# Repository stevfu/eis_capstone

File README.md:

# eis_capstone
Utilization of Electrochemical Impedance Spectroscopy for the Detection of Drugs

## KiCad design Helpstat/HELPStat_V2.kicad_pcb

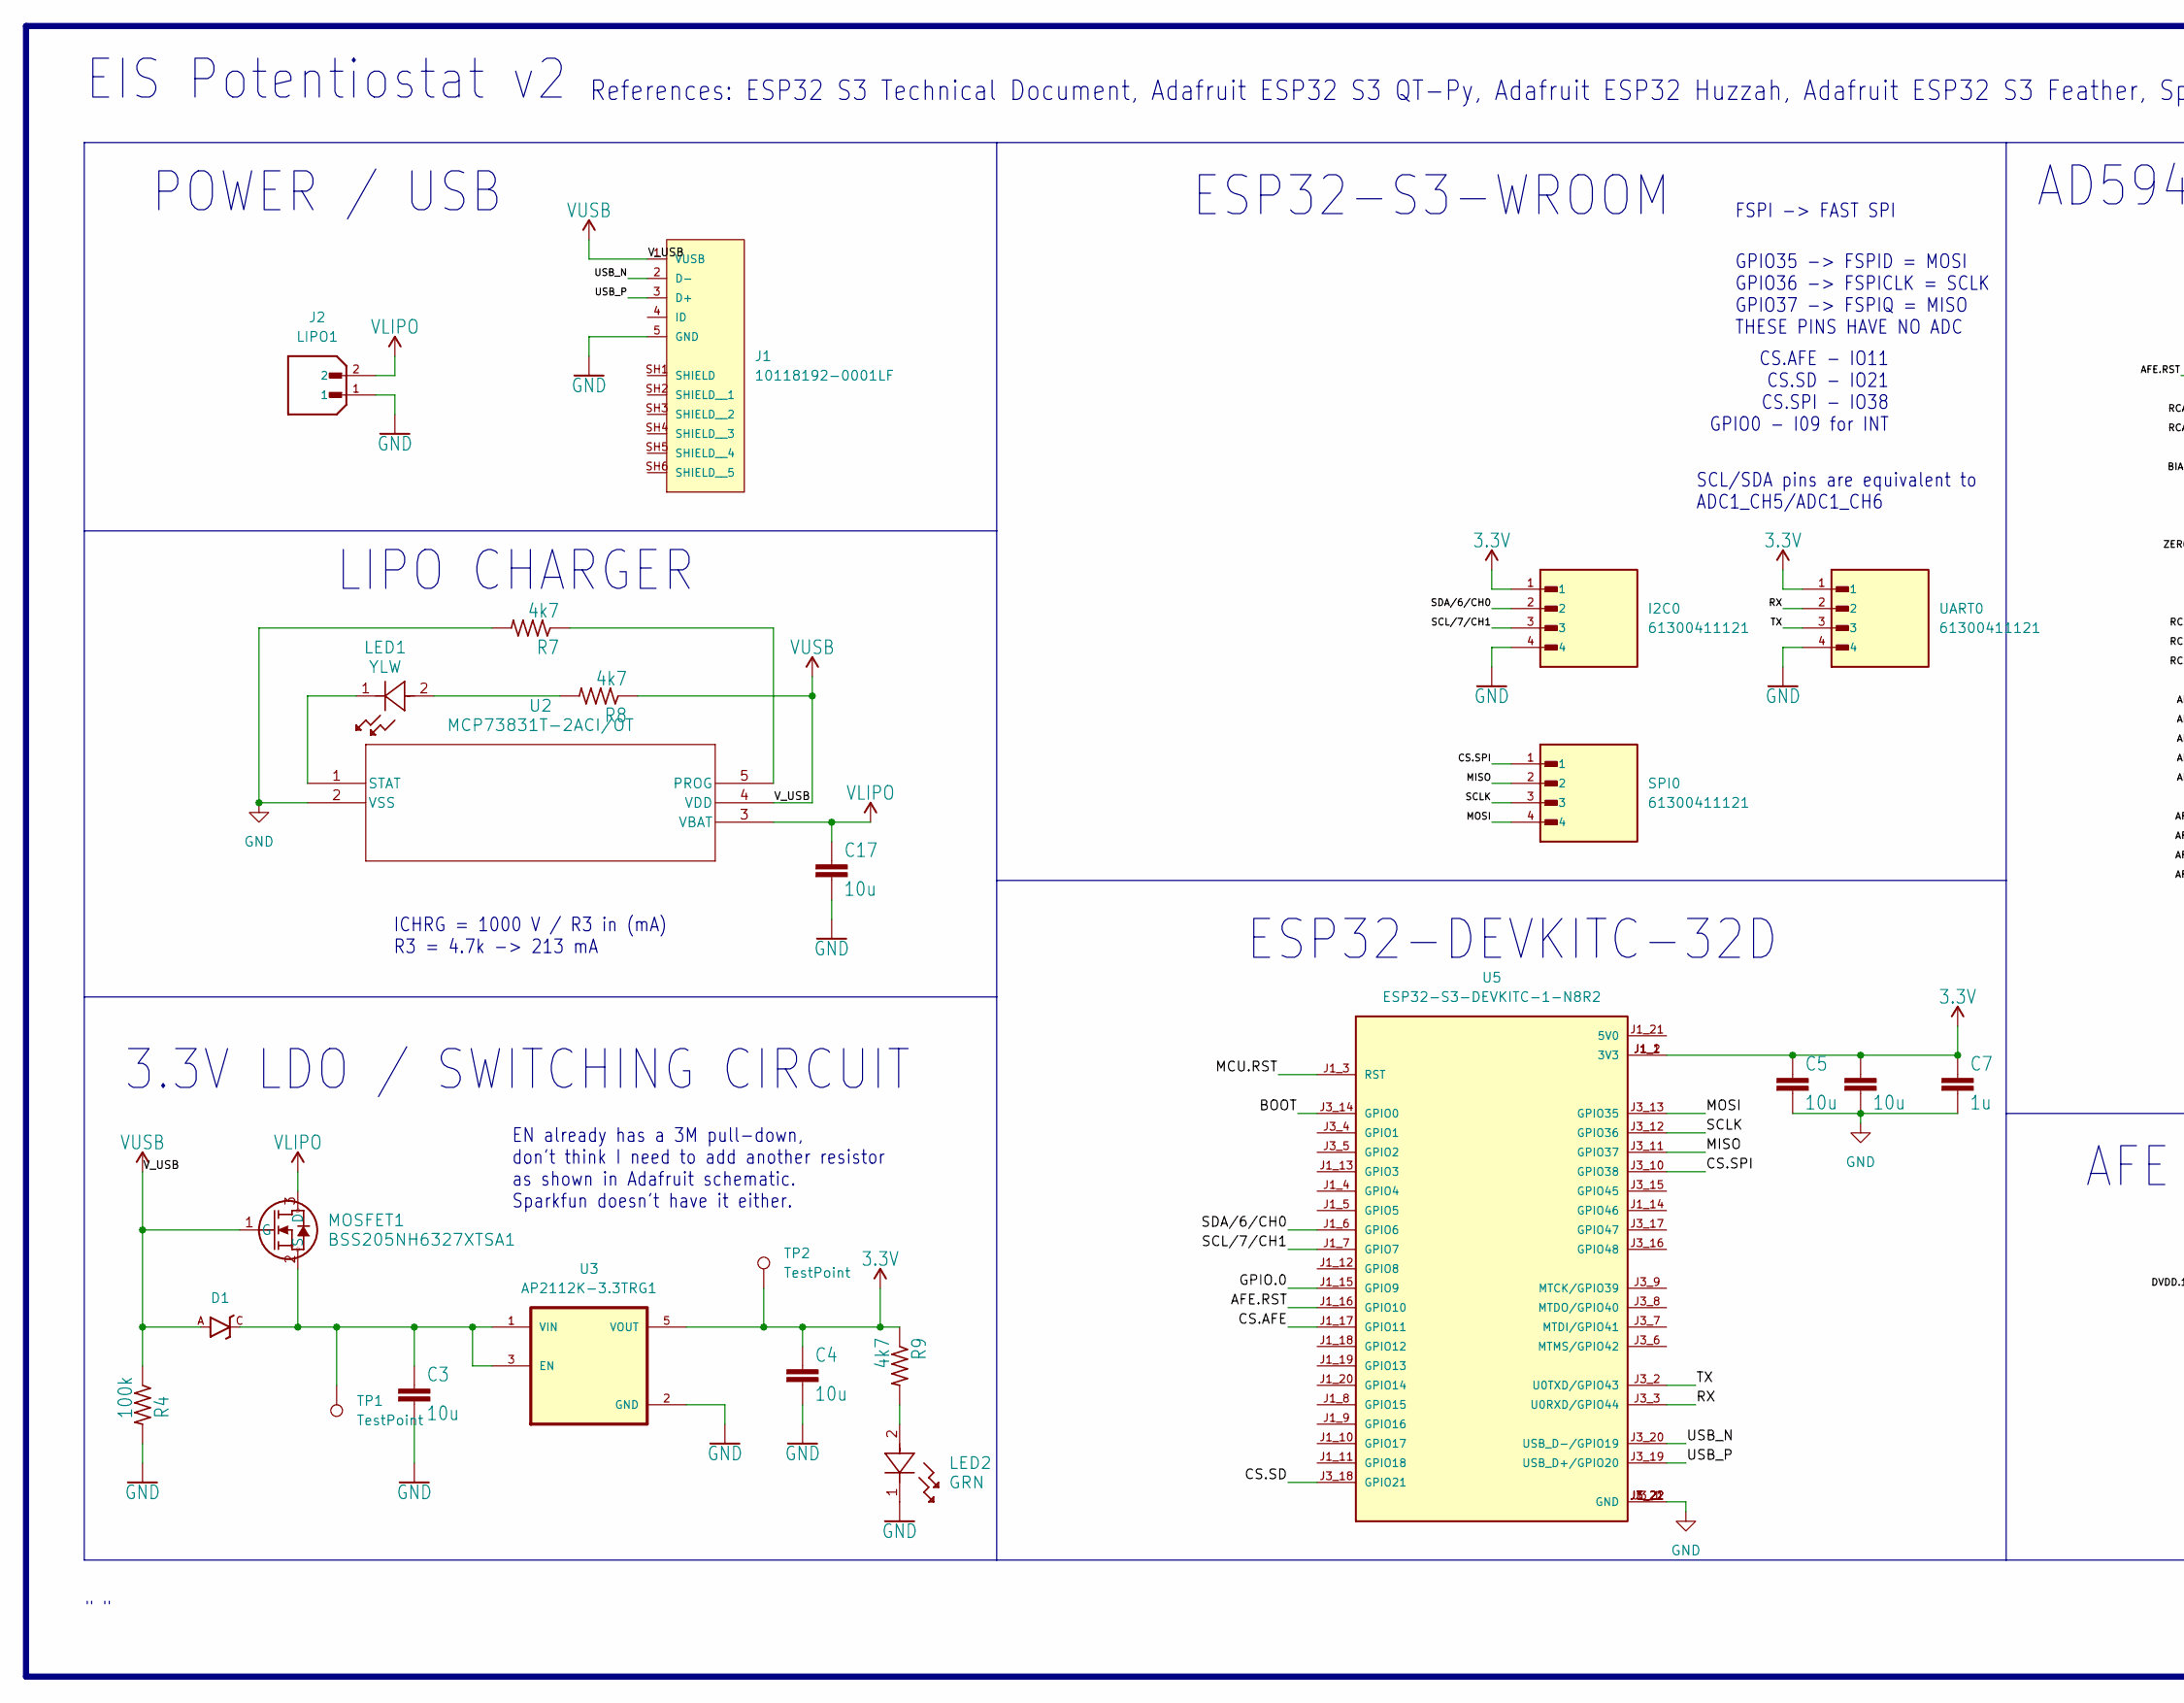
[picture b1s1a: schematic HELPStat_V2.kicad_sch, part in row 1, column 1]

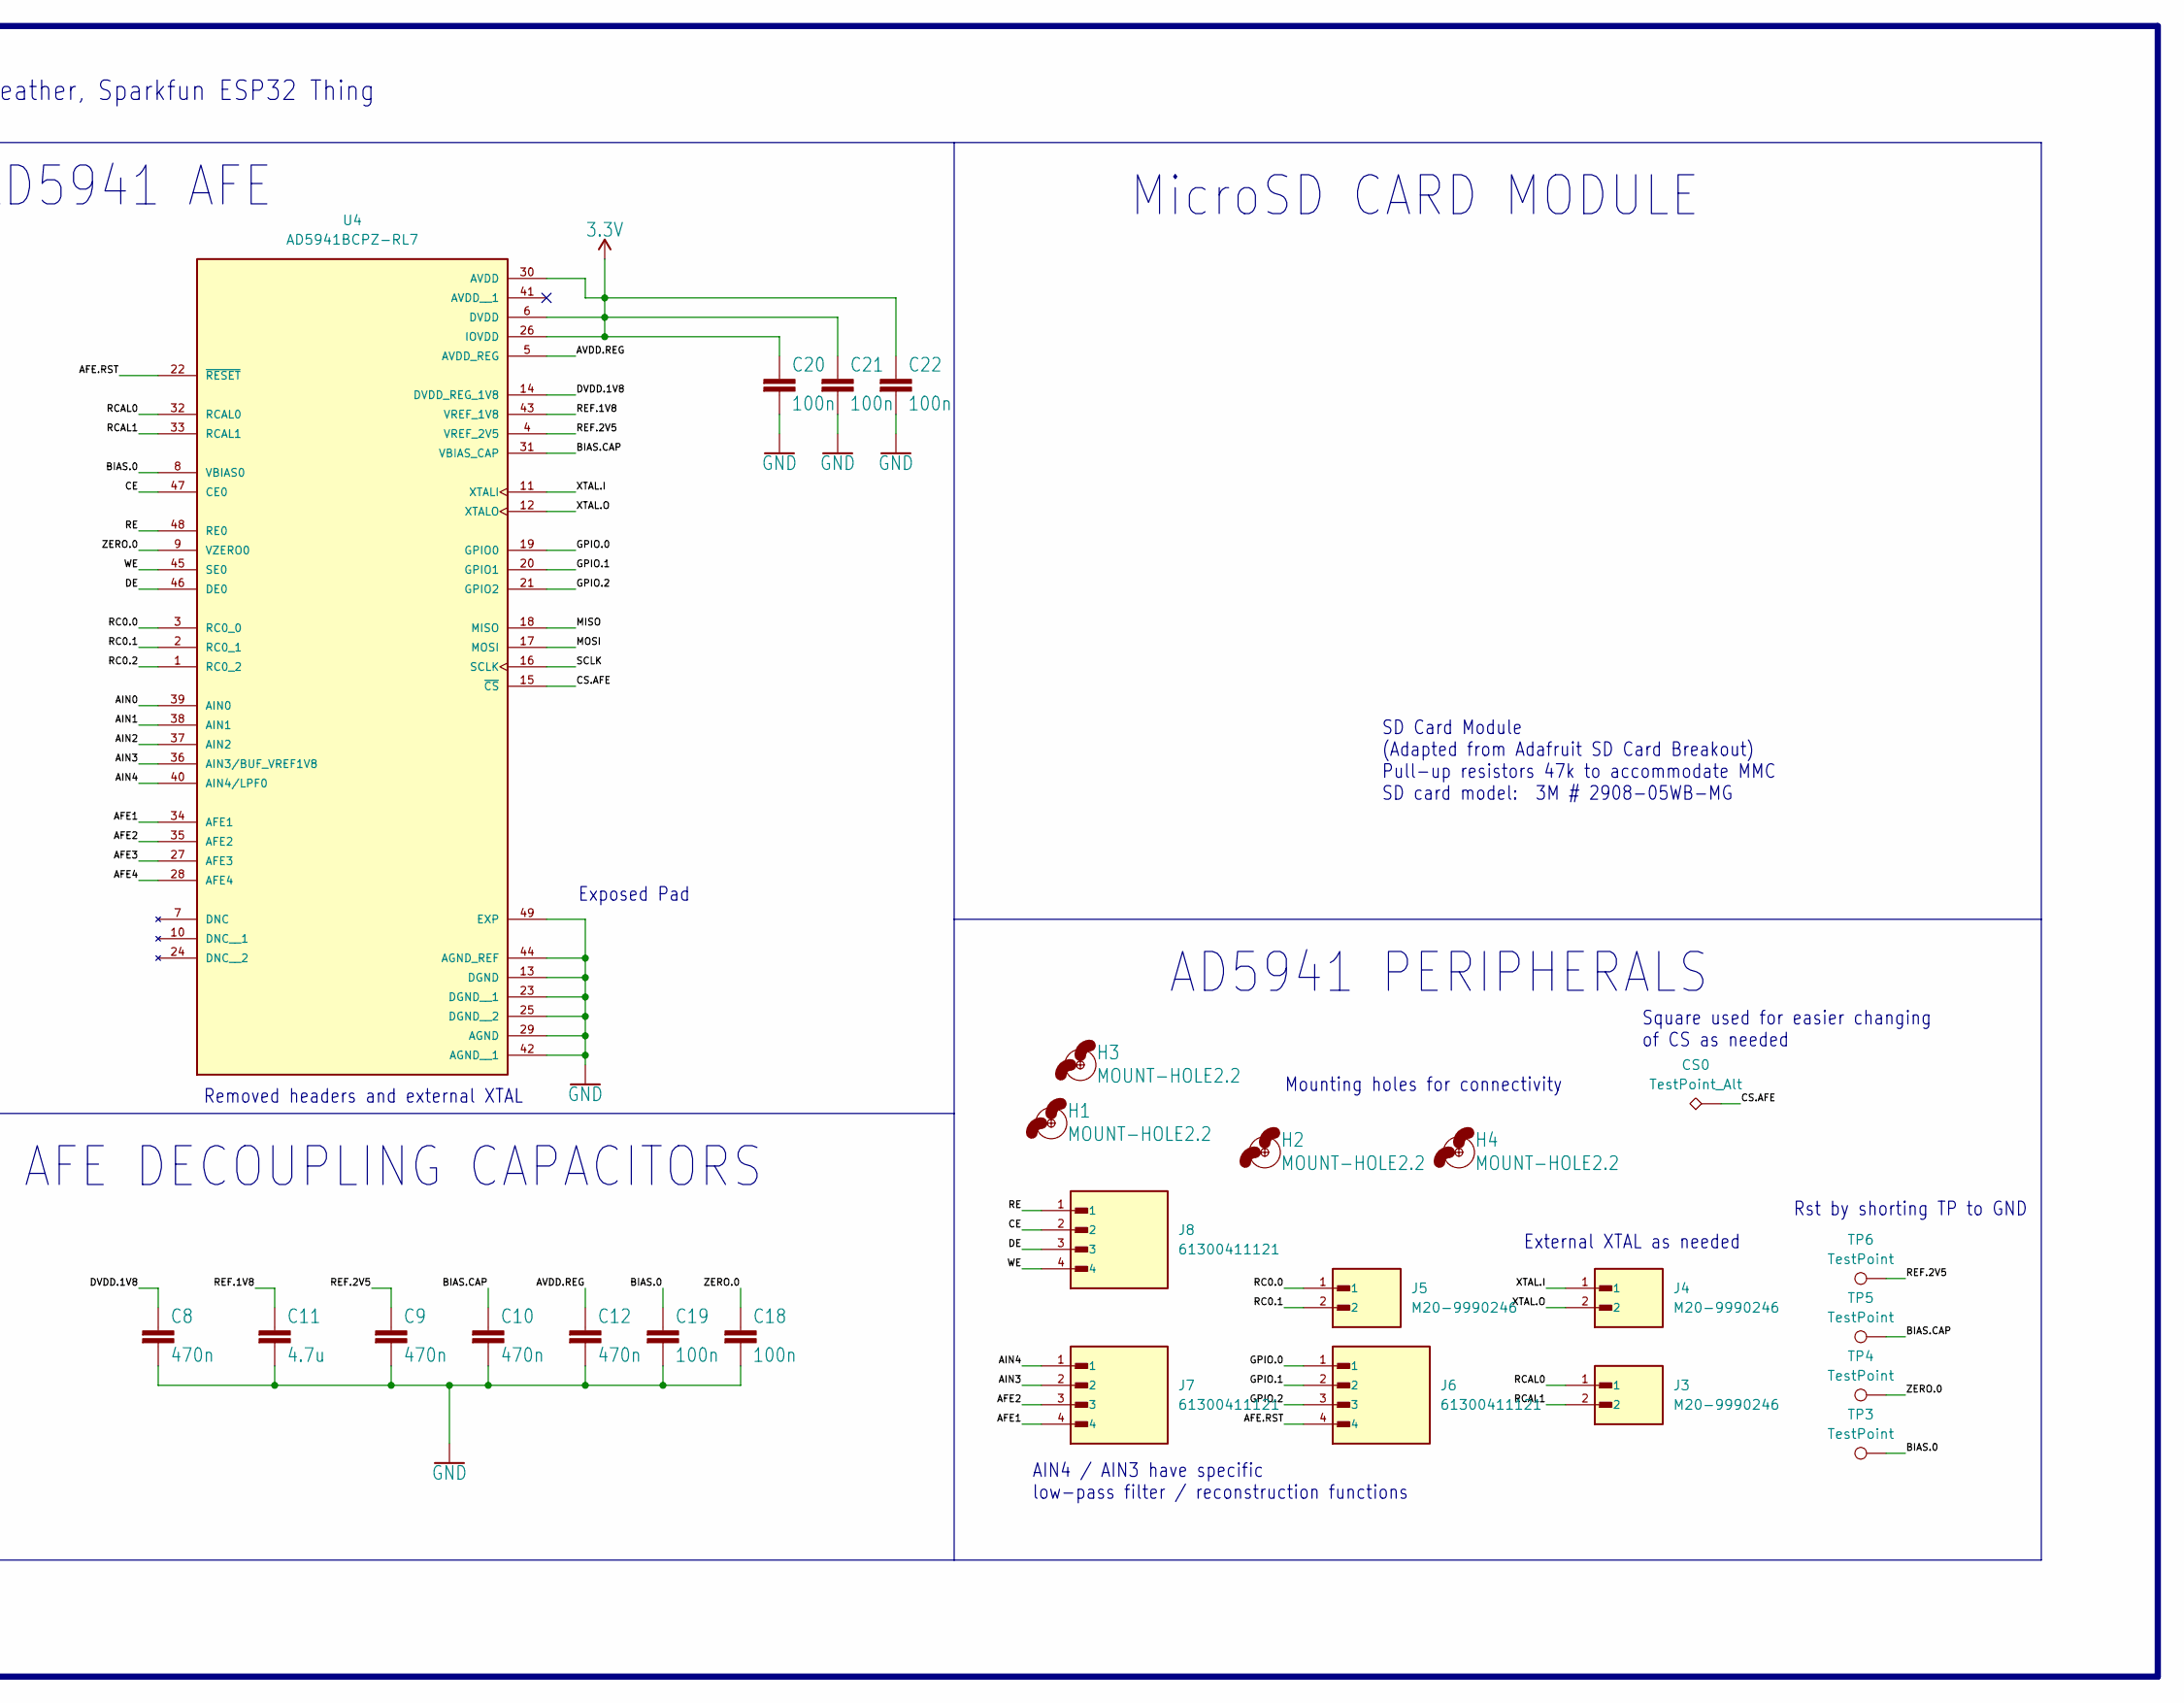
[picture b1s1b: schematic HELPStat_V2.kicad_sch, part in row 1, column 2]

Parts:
C3, C4, C5, C6, C17: 10u; C_0603_1608Metric; Part Number LMK107BBJ106MALT
C7: 1u; C_0603_1608Metric; Part Number CL10B105KP8NNNC
C8, C9, C10, C12: 470n; C_0603_1608Metric; Part Number TMK107B7474KA-TR
C11: 4.7u; C_0603_1608Metric; Part Number LMK107BJ475KA-T
C18, C19, C20, C21, C22: 100n; C_0603_1608Metric; Part Number CC0603KRX7R7BB104
CS0: TestPoint_Alt; TestPoint_Pad_2.0x2.0mm
D1: BAT20JFILM; SOD-323; Part Number BAT20JFILM
H1, H2, H3, H4: MOUNT-HOLE2.2; MountingHole_2.2mm_M2_Pad
I2C0: 61300411121; Part Number 61300411121
J1: 10118192-0001LF; AMPHENOL_10118192-0001LF; Part Number 10118192-0001LF
J2: LIPO1; JST_B2B-XH-A; Part Number B2B-XH-A:JST_B2B-XH-A
J3, J4, J5: M20-9990246; HARWIN_M20-9990246; Part Number M20-9990246
J6, J7, J8: 61300411121; Part Number 61300411121
LED1: YLW; LED_00-R18_OSR; Part Number GY PSLM31.13-HQHS-5F5G-L2M2-100-R18
LED2: GRN; LED_00-R18_OSR; Part Number GT PSLM31.13-HRHT-26-KM-100-R18
MOSFET1: BSS205NH6327XTSA1; PG-SOT23-3-5_INF; Part Number BSS205NH6327XTSA1
R4: 100k; R_0603_1608Metric; Part Number RC0603FR-07100KL
R7, R8, R9: 4k7; R_0603_1608Metric; Part Number RC0603FR-074K7L
SPI0: 61300411121; Part Number 61300411121
TP1, TP2, TP3, TP4, TP5, TP6: TestPoint; TestPoint_Pad_D1.0mm
U2: MCP73831T-2ACI/OT; SOT-23-5_MC_MCH; Part Number MCP73831T-2ACI/OT
U3: AP2112K-3.3TRG1; SOT95P285X140-5N; Part Number AP2112K-3.3TRG1
U4: AD5941BCPZ-RL7; QFN50P700X700X80-49N; Part Number AD5941BCPZ-RL7
U5: ESP32-S3-DEVKITC-1-N8R2; XCVR_ESP32-S3-DEVKITC-1-N8R2; Part Number ESP32-S3-DEVKITC-1-N8R2
UART0: 61300411121; Part Number 61300411121

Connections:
3.3V: C4.1, C5.1, C6.1, C7.1, C20.1, C21.1, C22.1, I2C0.1, R9.1, TP2.1, U3.5 (VOUT), U4.6 (DVDD), U4.26 (IOVDD), U4.30 (AVDD), U5.J1_1 (3V3), U5.J1_2 (3V3), UART0.1
/AFE1: J7.4, U4.34 (AFE1)
/AFE2: J7.3, U4.35 (AFE2)
/AFE3: U4.27 (AFE3)
/AFE4: U4.28 (AFE4)
/AFE.RST: J6.4, U4.22 (~RESET), U5.J1_16 (GPIO10)
/AIN0: U4.39 (AIN0)
/AIN1: U4.38 (AIN1)
/AIN2: U4.37 (AIN2)
/AIN3: J7.2, U4.36 (AIN3/BUF_VREF1V8)
/AIN4: J7.1, U4.40 (AIN4/LPF0)
/AVDD.REG: C12.1, U4.5 (AVDD_REG)
/BIAS.0: C19.1, TP3.1, U4.8 (VBIAS0)
/BIAS.CAP: C10.1, TP5.1, U4.31 (VBIAS_CAP)
/BOOT: U5.J3_14 (GPIO0)
/CE: J8.2, U4.47 (CE0)
/CS.AFE: CS0.1, U4.15 (~CS), U5.J1_17 (GPIO11)
/CS.SD: U5.J3_18 (GPIO21)
/CS.SPI: SPI0.1, U5.J3_10 (GPIO38)
/DE: J8.3, U4.46 (DE0)
/DVDD.1V8: C8.1, U4.14 (DVDD_REG_1V8)
/GPIO.0: J6.1, U4.19 (GPIO0), U5.J1_15 (GPIO9)
/GPIO.1: J6.2, U4.20 (GPIO1)
/GPIO.2: J6.3, U4.21 (GPIO2)
/MCU.RST: U5.J1_3 (RST)
/MISO: SPI0.2, U4.18 (MISO), U5.J3_11 (GPIO37)
/MOSI: SPI0.4, U4.17 (MOSI), U5.J3_13 (GPIO35)
/RC0.0: J5.1, U4.3 (RC0_0)
/RC0.1: J5.2, U4.2 (RC0_1)
/RC0.2: U4.1 (RC0_2)
/RCAL0: J3.1, U4.32 (RCAL0)
/RCAL1: J3.2, U4.33 (RCAL1)
/RE: J8.1, U4.48 (RE0)
/REF.1V8: C11.1, U4.43 (VREF_1V8)
/REF.2V5: C9.1, TP6.1, U4.4 (VREF_2V5)
/RX: U5.J3_3 (U0RXD/GPIO44), UART0.2
/SCLK: SPI0.3, U4.16 (SCLK), U5.J3_12 (GPIO36)
/TX: U5.J3_2 (U0TXD/GPIO43), UART0.3
/USB_N: J1.2 (D-), U5.J3_20 (USB_D-/GPIO19)
/USB_P: J1.3 (D+), U5.J3_19 (USB_D+/GPIO20)
/WE: J8.4, U4.45 (SE0)
/XTAL.I: J4.1, U4.11 (XTALI)
/XTAL.O: J4.2, U4.12 (XTALO)
/ZERO.0: C18.1, TP4.1, U4.9 (VZERO0)
GND: C3.2, C4.2, C5.2, C6.2, C7.2, C8.2, C9.2, C10.2, C11.2, C12.2, C17.2, C18.2, C19.2, C20.2, C21.2, C22.2, I2C0.4, J1.5 (GND), J2.1, LED2.1, R4.2, R7.2, U2.2 (VSS), U3.2 (GND), U4.13 (DGND), U4.23 (DGND__1), U4.25 (DGND__2), U4.29 (AGND), U4.42 (AGND__1), U4.44 (AGND_REF), U4.49 (EXP), U5.J1_22 (GND), U5.J3_1 (GND), U5.J3_21 (GND), U5.J3_22 (GND), UART0.4
unnamed: LED1.2, R8.2
unnamed: LED2.2, R9.2
unnamed: C3.1, D1.C, MOSFET1.2 (S), TP1.1, U3.1 (VIN), U3.3 (EN)
unnamed: R7.1, U2.5 (PROG)
unnamed: LED1.1, U2.1 (STAT)
VLIPO: C17.1, J2.2, MOSFET1.3 (D), U2.3 (VBAT)
VUSB: D1.A, J1.1 (VUSB), MOSFET1.1 (G), R4.1, R8.1, U2.4 (VDD)

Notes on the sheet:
MicroSD CARD MODULE
Rst by shorting TP to GND
ESP32-S3-WROOM
EN already has a 3M pull-down, don't think I need to add another resistor as shown in Adafruit schematic. Sparkfun doesn't have it either.
AD5941 PERIPHERALS
ICHRG = 1000 V / R3 in (mA) R3 = 4.7k -> 213 mA
AIN4 / AIN3 have specific low-pass filter / reconstruction functions
Mounting holes for connectivity
CS.AFE - IO11 CS.SD - IO21 CS.SPI - IO38 GPIO0 - I09 for INT
AFE DECOUPLING CAPACITORS
POWER / USB
LIPO CHARGER
Exposed Pad
SCL/SDA pins are equivalent to ADC1_CH5/ADC1_CH6
AD5941 AFE
" "
Square used for easier changing of CS as needed
3.3V LDO / SWITCHING CIRCUIT
References: ESP32 S3 Technical Document, Adafruit ESP32 S3 QT-Py, Adafruit ESP32 Huzzah, Adafruit ESP32 S3 Feather, Sparkfun ESP32 Thing
External XTAL as needed
EIS Potentiostat v2
ESP32-DEVKITC-32D
SD Card Module (Adapted from Adafruit SD Card Breakout) Pull-up resistors 47k to accommodate MMC SD card model: 3M # 2908-05WB-MG
Removed headers and external XTAL
GPIO35 -> FSPID = MOSI GPIO36 -> FSPICLK = SCLK GPIO37 -> FSPIQ = MISO THESE PINS HAVE NO ADC
FSPI -> FAST SPI

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
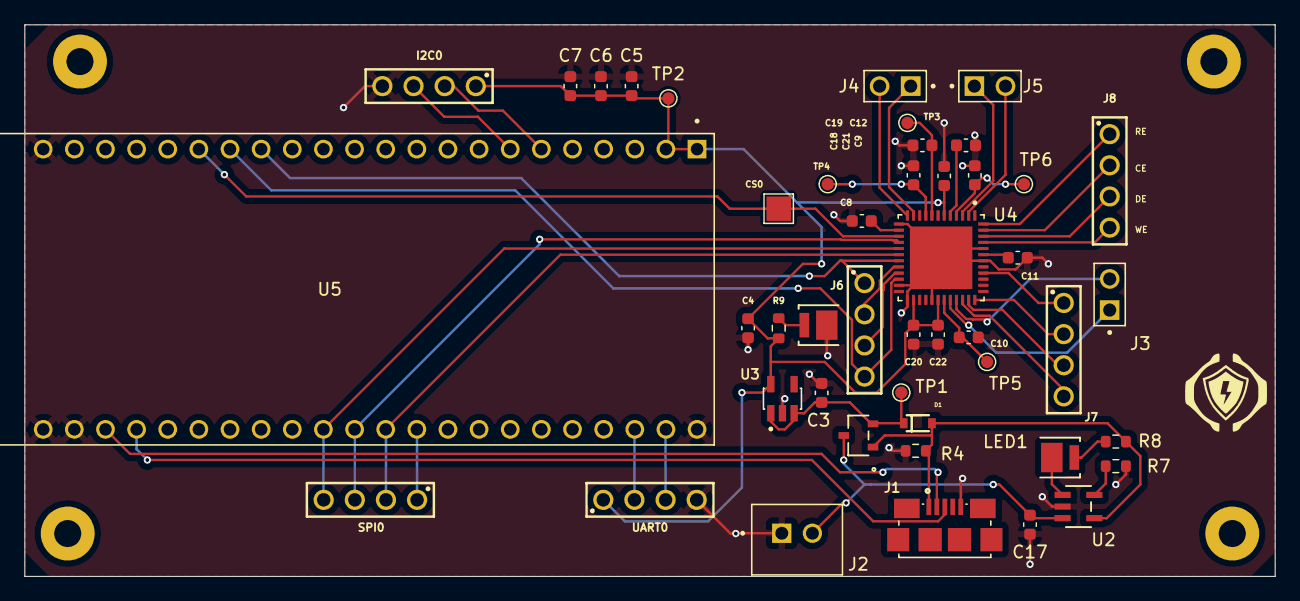
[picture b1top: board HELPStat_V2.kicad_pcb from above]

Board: 2 copper layers, 102.0 x 45.0 mm, 50 parts (0 on the bottom side), 45 nets.

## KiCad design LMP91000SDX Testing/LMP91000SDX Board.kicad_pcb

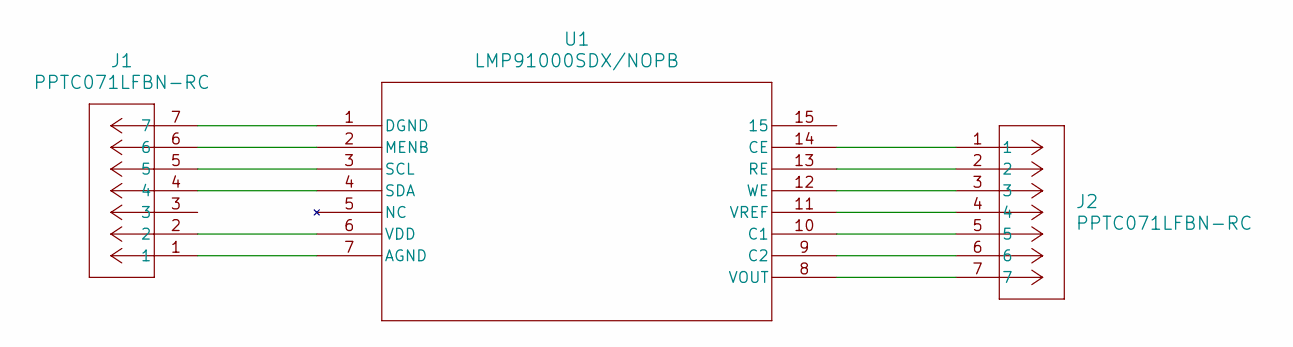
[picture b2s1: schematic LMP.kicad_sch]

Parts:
J1, J2: PPTC071LFBN-RC; CONN_xPxC071LFBN-RC_SUL
U1: LMP91000SDX/NOPB; SDA14B

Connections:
unnamed: J1.1, U1.7 (AGND)
unnamed: J2.5, U1.10 (C1)
unnamed: J2.6, U1.9 (C2)
unnamed: J2.1, U1.14 (CE)
unnamed: J1.7, U1.1 (DGND)
unnamed: J1.6, U1.2 (MENB)
unnamed: J2.2, U1.13 (RE)
unnamed: J1.5, U1.3 (SCL)
unnamed: J1.4, U1.4 (SDA)
unnamed: J1.2, U1.6 (VDD)
unnamed: J2.7, U1.8 (VOUT)
unnamed: J2.4, U1.11 (VREF)
unnamed: J2.3, U1.12 (WE)

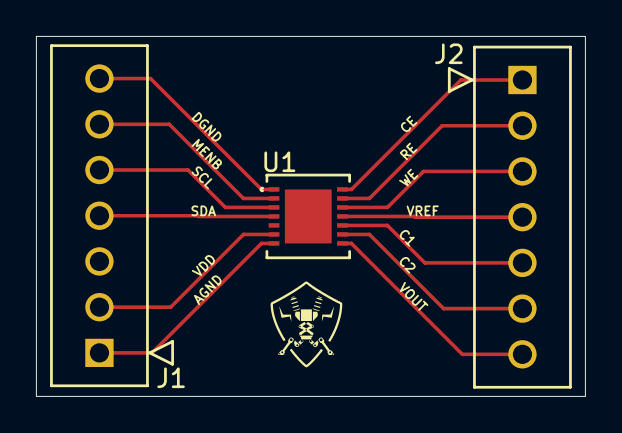
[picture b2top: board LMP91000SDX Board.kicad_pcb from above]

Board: 2 copper layers, 30.5 x 20.0 mm, 3 parts (0 on the bottom side), 13 nets.

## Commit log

2025-03-07 intial commit
2025-03-18 LMP91000SDX Testing
2025-03-19 Testing Board Completed
2025-03-24 Schematic Edits
2025-03-25 Added LMP USP-UART
2025-03-25 LMP USB Update
2025-03-25 deleted laptop duplicates
2025-04-24 Andrew Edits
2025-04-24 Sch Draft Completed
2025-04-25 added firmware template and pcb
2025-04-26 more pcb changes
2025-04-26 BOM CSV added
2025-04-26 CSV and SCH edits
2025-04-28 PCB Touches
2025-04-29 PCB Editted Routes
2025-04-30 Gibby Bub
2025-05-09 pcb v2
2025-05-10 Sch and PCB cleanup/fixes
2025-05-21 extra PCB changes
2025-05-27 working pcb code
2025-06-04 new software
2025-06-11 revisions i think
2025-06-11 hmhmhmhhm
2025-06-26 kk
    kk transform
2025-06-26 ECM calculations
    ECM
2025-06-27 ecm stuffs
2025-06-27 organization, new firmware scripts
2025-06-29 ecm fitting function
    trials
2025-06-30 test cases
2025-07-01 new filter
2025-07-04 changes to .ino script
2025-07-04 new firmware version
2025-07-06 DATA PROCESSING
2025-07-11 testing script organization changes
2025-07-13 changes to data
2025-07-15 sophisticated works
2025-07-15 local revision of firmware
2025-07-16 testing w beer and substances
2025-07-17 added list of references
2025-07-24 some final organizational changes
2025-07-31 final report changes
